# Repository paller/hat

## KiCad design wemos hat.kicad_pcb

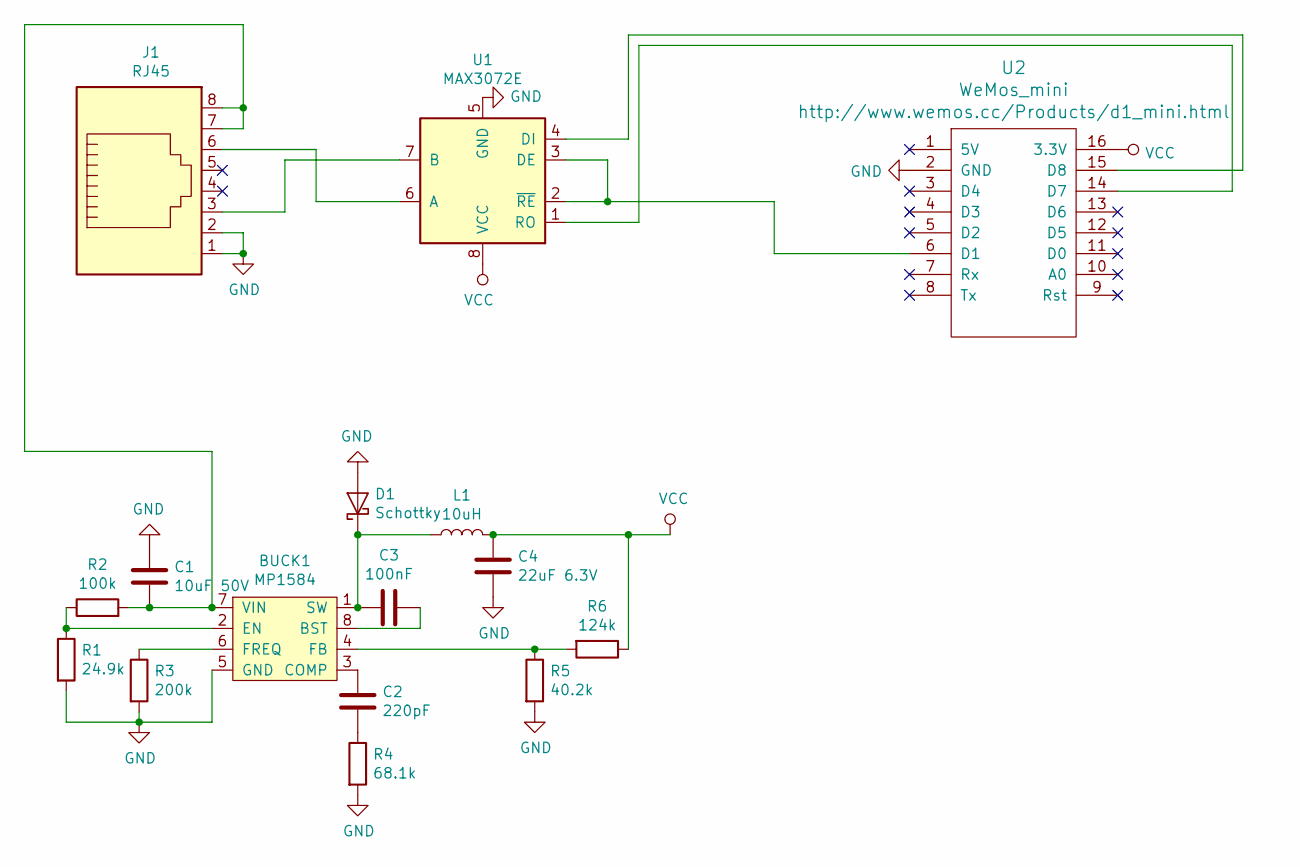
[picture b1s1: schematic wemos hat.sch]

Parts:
BUCK1: MP1584; SOIC-8_3.9x4.9mm_P1.27mm
C1: 10uF 50V; C_1206_3216Metric
C2: 220pF; C_0603_1608Metric
C3: 100nF; C_0603_1608Metric
C4: 22uF 6.3V; C_0603_1608Metric
D1: Schottky; D_SMA
J1: RJ45; RJ45_Amphenol_54602-x08_Horizontal
L1: 10uH; L_Sunlord_MWSA0518_5.4x5.2mm
R1: 24.9k; R_0603_1608Metric
R2: 100k; R_0603_1608Metric
R3: 200k; R_0603_1608Metric
R4: 68.1k; R_0603_1608Metric
R5: 40.2k; R_0603_1608Metric
R6: 124k; R_0603_1608Metric
U1: MAX3072E; SOIC-8_3.9x4.9mm_P1.27mm
U2: WeMos_mini; wemos-d1-mini-connectors-only

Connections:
GND: BUCK1.5 (GND), C1.1, C4.2, D1.2 (A), J1.1, J1.2, R1.2, R3.2, R4.2, R5.2, U1.5 (GND), U2.2 (GND)
unnamed: BUCK1.1 (SW), C3.2, D1.1 (K), L1.1
unnamed: BUCK1.2 (EN), R1.1, R2.1
unnamed: BUCK1.3 (COMP), C2.1
unnamed: BUCK1.4 (FB), R5.1, R6.2
unnamed: BUCK1.6 (FREQ), R3.1
unnamed: BUCK1.7 (VIN), C1.2, J1.7, J1.8, R2.2
unnamed: BUCK1.8 (BST), C3.1
unnamed: C2.2, R4.1
unnamed: J1.3, U1.7 (B)
unnamed: J1.6, U1.6 (A)
unnamed: U1.1 (RO), U2.14 (D7)
unnamed: U1.2 (~RE~), U1.3 (DE), U2.6 (D1)
unnamed: U1.4 (DI), U2.15 (D8)
VCC: C4.1, L1.2, R6.1, U1.8 (VCC), U2.16 (3.3V)

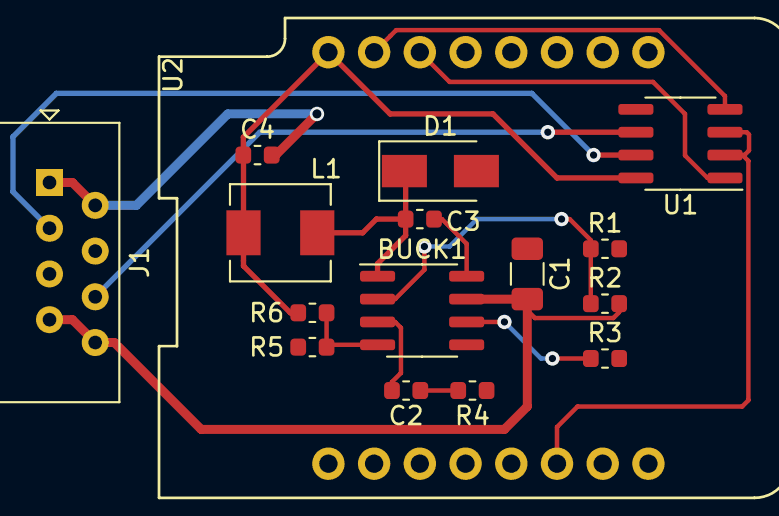
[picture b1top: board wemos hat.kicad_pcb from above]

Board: 2 copper layers, 16 parts (0 on the bottom side), 15 nets.

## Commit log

2019-12-08 git ignore
2019-12-08 Something new
2019-12-09 Components done
